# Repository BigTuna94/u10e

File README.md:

# μ10e

The μ10e, pronounced *Mutiny*, is another take on a DIY ergonomic ortholinear with column stagger split keyboard inspired by such boards as the ErgoDox, Crkbd, Splitreus62, and even the Planck and Boardwalk.

### Sample Layout

### Current PCB Design

### Goals
The initial inspiration for this board was a Crkbd with 1.5U modifiers, a number row, and Kailh Choc sockets. However, after seeing designs like the Lily58, I've decided it would be even better to support both Choc and MX sockets on the same pcb.

Although the first revision of this board will use a socketed Pro Micro footprint MCU per side, the overall goal of this project is something a little more sofisticated.

### Roadmap
- [x] Create initial schematic and pcb design using pro micro
- [ ] Gather feedback from community

### Potential Future Features
- Encoder footprint below controller
- Move TRRS footprint
- OLED footprint below contoller
- Built in MCU
  - The nice!nano and other new USB-C boards are really good right now.
  - Even though I like this idea, I'll see if there is community interest

### rev1.0 Images
#### MX Mounts

#### Choc Mounts

#### Socket Closeup

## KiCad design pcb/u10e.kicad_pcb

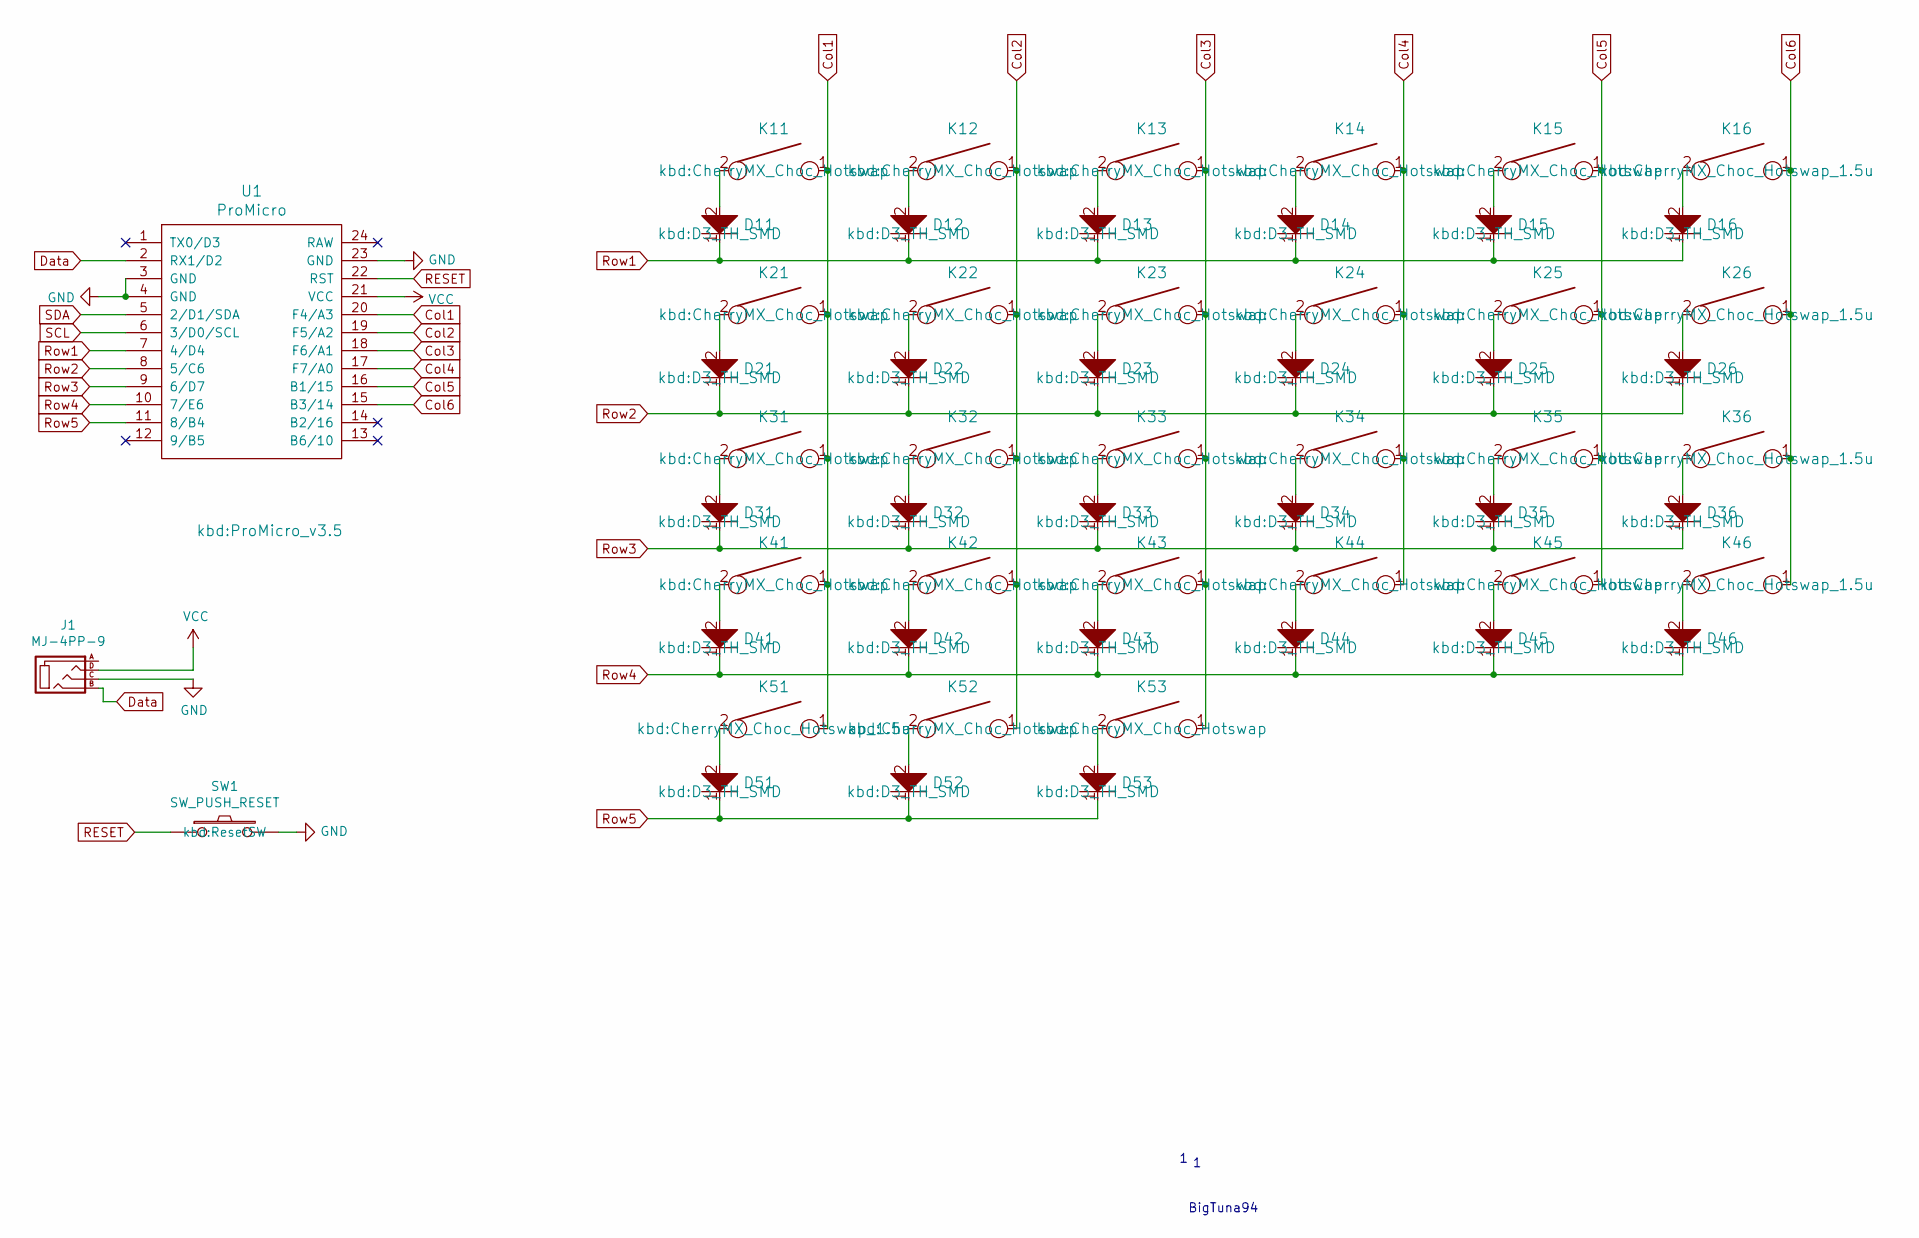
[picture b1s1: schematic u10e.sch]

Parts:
D11, D12, D13, D14, D15, D16, D21, D22, D23, D24, D25, D26, D31, D32, D33, D34, D35, D36, D41, D42, D43, D44, D45, D46, D51, D52, D53: D; D3_TH_SMD
J1: MJ-4PP-9
K11, K12, K13, K14, K15, K21, K22, K23, K24, K25, K31, K32, K33, K34, K35, K41, K42, K43, K44, K45, K52, K53: KEYSW; CherryMX_Choc_Hotswap
K16, K26, K36, K46, K51: KEYSW; CherryMX_Choc_Hotswap_1.5u
SW1: SW_PUSH_RESET; ResetSW
U1: ProMicro; ProMicro_v3.5

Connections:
Col1: K11.1, K21.1, K31.1, K41.1, K51.1, U1.20 (F4/A3)
Col2: K12.1, K22.1, K32.1, K42.1, K52.1, U1.19 (F5/A2)
Col3: K13.1, K23.1, K33.1, K43.1, K53.1, U1.18 (F6/A1)
Col4: K14.1, K24.1, K34.1, K44.1, U1.17 (F7/A0)
Col5: K15.1, K25.1, K35.1, K45.1, U1.16 (B1/15)
Col6: K16.1, K26.1, K36.1, K46.1, U1.15 (B3/14)
Data: J1.B, U1.2 (RX1/D2)
GND: J1.C, SW1.2, U1.3 (GND), U1.4 (GND), U1.23 (GND)
unnamed: D11.2, K11.2
unnamed: D12.2, K12.2
unnamed: D13.2, K13.2
unnamed: D14.2, K14.2
unnamed: D15.2, K15.2
unnamed: D16.2, K16.2
unnamed: D21.2, K21.2
unnamed: D22.2, K22.2
unnamed: D23.2, K23.2
unnamed: D24.2, K24.2
unnamed: D25.2, K25.2
unnamed: D26.2, K26.2
unnamed: D31.2, K31.2
unnamed: D32.2, K32.2
unnamed: D33.2, K33.2
unnamed: D34.2, K34.2
unnamed: D35.2, K35.2
unnamed: D36.2, K36.2
unnamed: D41.2, K41.2
unnamed: D42.2, K42.2
unnamed: D43.2, K43.2
unnamed: D44.2, K44.2
unnamed: D45.2, K45.2
unnamed: D46.2, K46.2
unnamed: D51.2, K51.2
unnamed: D52.2, K52.2
unnamed: D53.2, K53.2
RESET: SW1.1, U1.22 (RST)
Row1: D11.1, D12.1, D13.1, D14.1, D15.1, D16.1, U1.7 (4/D4)
Row2: D21.1, D22.1, D23.1, D24.1, D25.1, D26.1, U1.8 (5/C6)
Row3: D31.1, D32.1, D33.1, D34.1, D35.1, D36.1, U1.9 (6/D7)
Row4: D41.1, D42.1, D43.1, D44.1, D45.1, D46.1, U1.10 (7/E6)
Row5: D51.1, D52.1, D53.1, U1.11 (8/B4)
SCL: U1.6 (3/D0/SCL)
SDA: U1.5 (2/D1/SDA)
VCC: J1.D, U1.21 (VCC)

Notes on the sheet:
BigTuna94

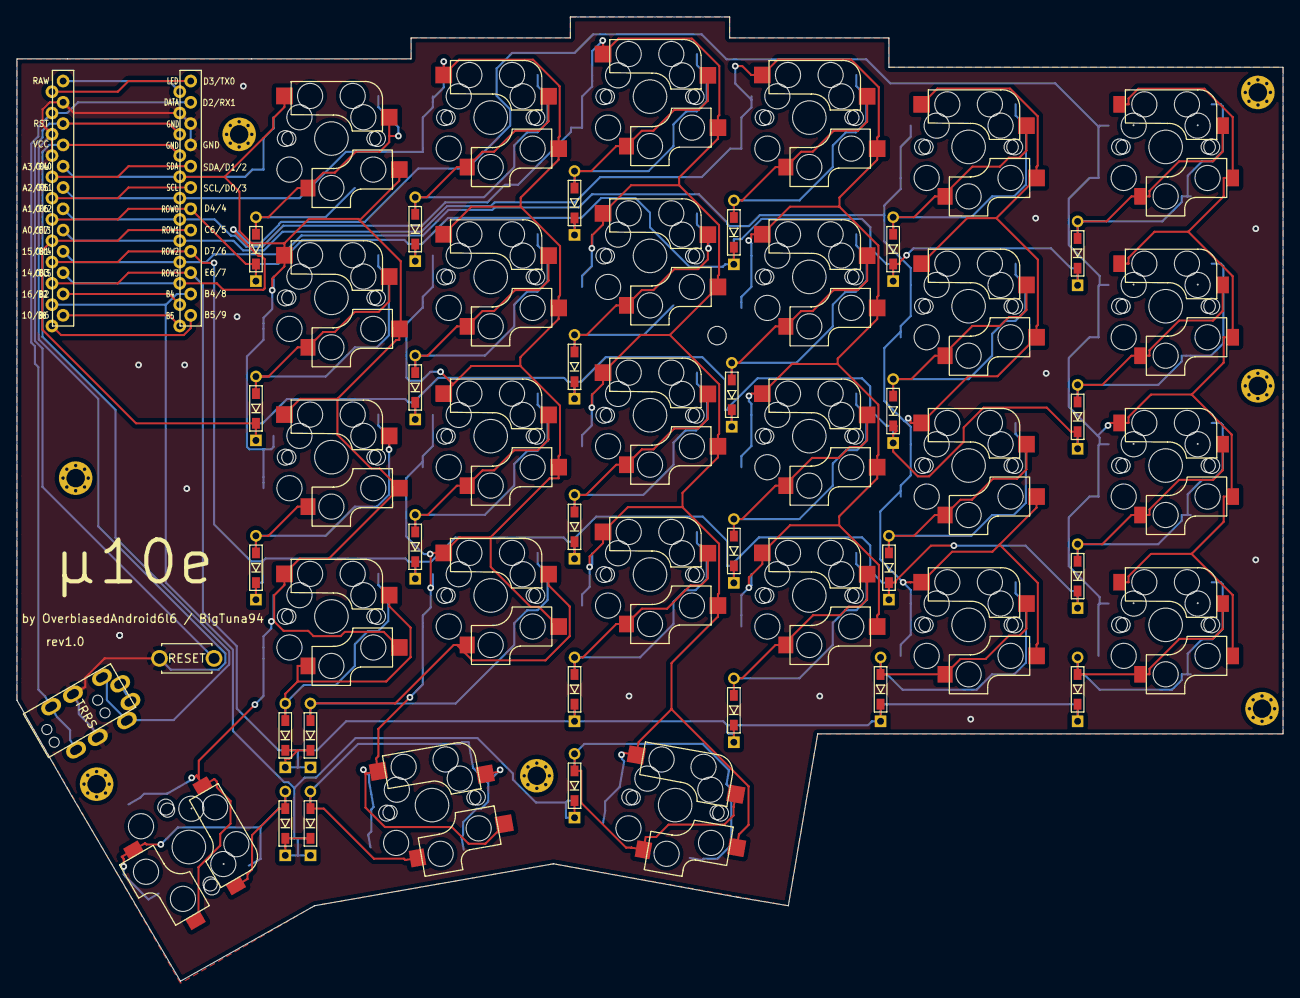
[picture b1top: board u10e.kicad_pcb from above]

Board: 2 copper layers, 151.0 x 115.0 mm, 65 parts (0 on the bottom side), 42 nets.

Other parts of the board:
M1, M2, M4, M5, M6, M7, M8: M2_HOLE_v3
M3: MountingHole_2.2mm_M2

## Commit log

2020-09-24 added layout to readme
2020-09-24 Added submodules for libs used
2020-09-24 Added current pcb design - schematic complete, parts placed on board but wires not routed
2020-09-24 updated keyboard layout image, added layout json
2020-09-24 removed bad layout image
2020-09-24 added new layout image
2020-09-25 moved bottom row to more evenly distribute x space
2020-09-25 added r1 edgecuts
2020-09-26 pre routing commit
2020-09-26 added routes
2020-09-26 Revert "added routes"
    This reverts commit ca254ce08e903a7b231e3a80e900436ff372913d.
2020-09-26 removed bak file
2020-09-26 Added mounting holes
2020-09-27 Added routes and silkscreens
2020-09-27 updated status
2020-09-27 added pcb image
2020-11-10 updated readme, added rev1.0 images
2021-07-12 initial case bottom
2021-07-13 final adjustments for fitment
2021-07-13 bottom updates, added topplate
2021-07-14 refactored case bottom to center properly
